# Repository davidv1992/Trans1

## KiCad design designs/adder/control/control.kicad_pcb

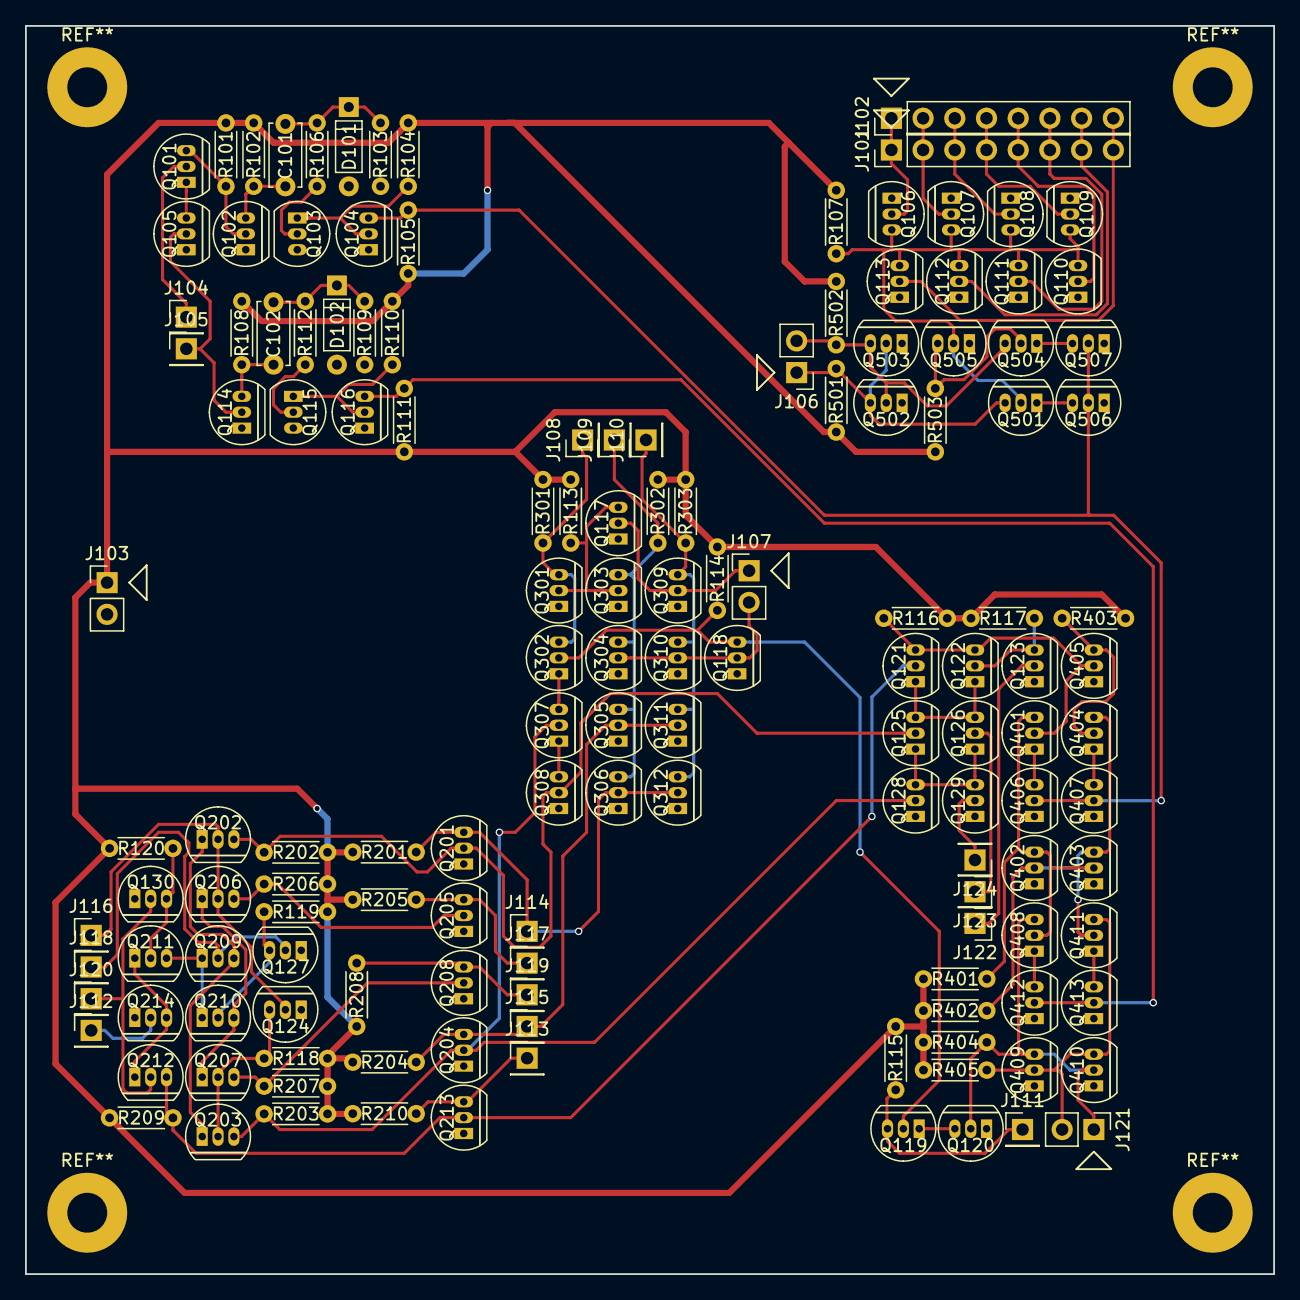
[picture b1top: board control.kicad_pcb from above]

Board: 2 copper layers, 100.0 x 100.0 mm, 145 parts (0 on the bottom side), 78 nets.

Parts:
C101, C102: 4.7nF; C_default
D101, D102: 1N4148; D_default
J101, J102: Conn_01x08; PH_1x8
J103: Conn_01x02_Power; PH_1x2
J104, J105, J108, J109, J110, J111, J112, J113, J114, J115, J116, J117, J118, J119, J120, J122, J123, J124: Conn_01x01; PH_1x1
J106, J107, J121: Conn_01x02; PH_1x2
Q101, Q102, Q104, Q105, Q106, Q107, Q108, Q109, Q110, Q111, Q112, Q113, Q114, Q116, Q117, Q118, Q119, Q120, Q121, Q122, Q123, Q124, Q125, Q126, Q127, Q128, Q129, Q130, Q201, Q202, Q203, Q204, Q205, Q206, Q207, Q208, Q209, Q210, Q211, Q212, Q213, Q214, Q301, Q302, Q303, Q304, Q305, Q306, Q307, Q308, Q309, Q310, Q311, Q312, Q401, Q402, Q403, Q404, Q405, Q406, Q407, Q408, Q409, Q410, Q411, Q412, Q413, Q501, Q502, Q503, Q504, Q505, Q506, Q507: 2N7000; TO-92-FET
Q103, Q115: BC547; TO-92-BJT
R101, R102, R104, R105, R107, R108, R110, R111, R113, R114, R115, R116, R117, R118, R119, R120, R201, R202, R203, R204, R205, R206, R207, R208, R209, R210, R301, R302, R303, R401, R402, R404, R405, R501, R502, R503: 1k; R_small
R103, R106, R109, R112: 10k; R_small
R403: R; R_small

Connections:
/BDEC/1en: J110.1, Q309.3, Q310.3, Q311.3, Q312.3, R303.2
/BDEC/Ben: J108.1, Q301.3, Q302.3, R301.2
/BDEC/LSH: J114.1, Q201.3, Q306.2, Q312.2, R201.2
/BDEC/RSH: J115.1, Q204.3, Q305.2, Q311.2, R204.2
/BDEC/b0: Q117.3, Q301.2, Q303.2, R113.2
/BDEC/b1: Q118.3, Q119.2, Q302.2, R114.2
/BDEC/~B~en: J109.1, Q303.3, Q304.3, Q305.3, Q306.3, R302.2
/BDEC/~LSH: Q125.2, Q201.2, Q202.3, Q308.2, R202.2
/BDEC/~RSH: Q128.2, Q203.3, Q204.2, Q307.2, R203.2
/BDEC/~b0: J107.1, Q117.2, Q309.2
/BDEC/~b1: J107.2, Q118.2, Q304.2, Q310.2
/Cstore/D: Q121.3, Q122.3, Q401.2, Q405.2, R116.2
/Cstore/Q: J121.1, Q120.2, Q408.3, Q409.3, Q410.2, R404.2
/Cstore/clk: Q104.3, Q406.2, Q407.2, Q506.2, Q507.2, R105.2
/Cstore/~Q: J121.2, Q409.2, Q410.3, Q411.3, R405.2
/Cstore/~clk: Q116.3, Q412.2, Q413.2, R111.2
/OutDEC/ADD: J113.1, Q213.3, R210.2
/OutDEC/AND: J117.1, Q205.3, R205.2
/OutDEC/AluEN: J112.1, Q214.2
/OutDEC/OR: J119.1, Q208.3, R208.2
/OutDEC/S0: Q124.3, Q203.2, Q207.2, R118.2
/OutDEC/S1: Q127.3, Q210.2, R119.2
/OutDEC/S2: Q130.3, Q211.2, R120.2
/OutDEC/~ADD: Q121.2, Q212.3, Q213.2, R209.2
/OutDEC/~AND: Q205.2, Q206.3, R206.2
/OutDEC/~OR: Q207.3, Q208.2, R207.2
/OutDEC/~S0: J116.1, Q124.2, Q202.2, Q206.2
/OutDEC/~S1: J118.1, Q127.2, Q209.2
/OutDEC/~S2: J120.1, Q130.2, Q212.2
/Zstore/D: Q106.3, Q107.3, Q108.3, Q109.3, Q110.3, Q111.3, Q112.3, Q113.3, Q501.2, Q505.2, R107.2
/Zstore/Q: J106.2, Q502.2, Q503.3, Q504.3, R502.2
/Zstore/~Q: J106.1, Q501.3, Q502.3, Q503.2, R501.2
GND: D101.2, D102.2, J103.2, Q102.1, Q103.3, Q104.1, Q105.1, Q106.1, Q107.1, Q108.1, Q109.1, Q110.1, Q111.1, Q112.1, Q113.1, Q114.1, Q115.3, Q116.1, Q117.1, Q118.1, Q120.1, Q123.1, Q124.1, Q127.1, Q128.1, Q129.1, Q130.1, Q201.1, Q204.1, Q205.1, Q208.1, Q213.1, Q214.1, Q301.1, Q303.1, Q304.1, Q305.1, Q306.1, Q308.1, Q309.1, Q310.1, Q311.1, Q312.1, Q402.1, Q403.1, Q405.1, Q406.1, Q407.1, Q409.1, Q410.1, Q412.1, Q413.1, Q502.1, Q503.1, Q505.1, Q506.1, Q507.1, R103.1, R109.1
unnamed: C101.1, D101.1, R103.2, R106.2
unnamed: C101.2, Q102.3, R102.2
unnamed: C102.1, D102.1, R109.2, R112.2
unnamed: C102.2, Q114.3, R108.2
unnamed: J101.1, J102.1, Q106.2
unnamed: J101.2, J102.2, Q107.2
unnamed: J101.3, J102.3, Q108.2
unnamed: J101.4, J102.4, Q109.2
unnamed: J101.5, J102.5, Q110.2
unnamed: J101.6, J102.6, Q111.2
unnamed: J101.7, J102.7, Q112.2
unnamed: J101.8, J102.8, Q113.2
unnamed: J104.1, Q101.2
unnamed: J105.1, Q105.2, Q114.2
unnamed: J111.1, Q119.3, R115.2
unnamed: J122.1, Q123.2
unnamed: J123.1, Q126.2
unnamed: J124.1, Q129.2
unnamed: Q101.1, Q105.3
unnamed: Q101.3, Q102.2, R101.2
unnamed: Q103.1, Q104.2, R104.2
unnamed: Q103.2, R106.1
unnamed: Q115.1, Q116.2, R110.2
unnamed: Q115.2, R112.1
unnamed: Q119.1, Q120.3
unnamed: Q121.1, Q122.1, Q125.3, Q126.3
unnamed: Q122.2, Q123.3, R117.2
unnamed: Q125.1, Q126.1, Q128.3, Q129.3
unnamed: Q202.1, Q203.1, Q209.3
unnamed: Q206.1, Q207.1, Q210.3
unnamed: Q209.1, Q210.1, Q211.3
unnamed: Q211.1, Q212.1, Q214.3
unnamed: Q302.1, Q307.3
unnamed: Q307.1, Q308.3
unnamed: Q401.1, Q406.3
unnamed: Q401.3, Q402.3, Q403.2, Q408.2, R401.2
unnamed: Q402.2, Q403.3, Q404.3, Q411.2, R402.2
unnamed: Q404.1, Q407.3
unnamed: Q404.2, Q405.3, R403.2
unnamed: Q408.1, Q412.3
unnamed: Q411.1, Q413.3
unnamed: Q501.1, Q506.3
unnamed: Q504.1, Q507.3
unnamed: Q504.2, Q505.3, R503.2
VCC: J103.1, R101.1, R102.1, R104.1, R105.1, R107.1, R108.1, R110.1, R111.1, R113.1, R114.1, R115.1, R116.1, R117.1, R118.1, R119.1, R120.1, R201.1, R202.1, R203.1, R204.1, R205.1, R206.1, R207.1, R208.1, R209.1, R210.1, R301.1, R302.1, R303.1, R401.1, R402.1, R403.1, R404.1, R405.1, R501.1, R502.1, R503.1

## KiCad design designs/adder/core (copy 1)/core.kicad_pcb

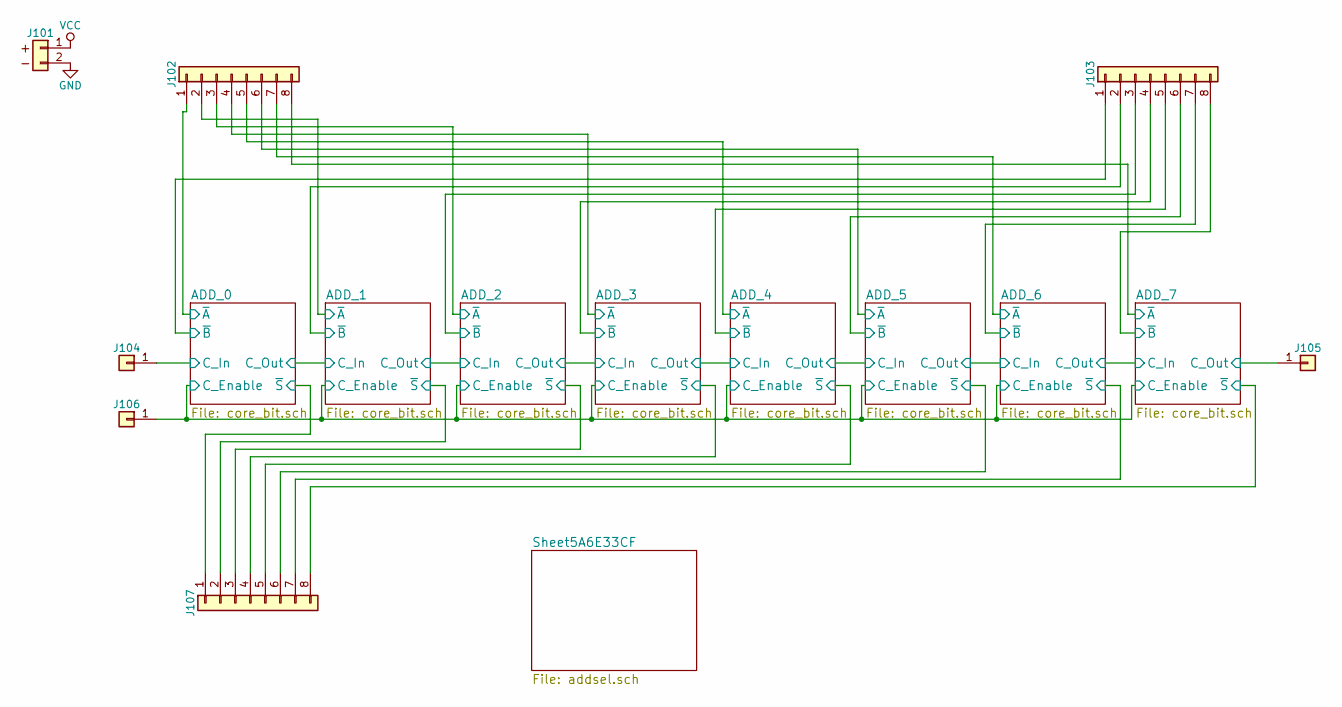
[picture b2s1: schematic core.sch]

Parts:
J101: Conn_01x02_Power; PH_1x2
J102, J103, J107: Conn_01x08; PH_1x8
J104, J105, J106: Conn_01x01; PH_1x1

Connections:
/ADD_0/C_Enable: J106.1; also elsewhere on the board
/ADD_0/C_In: J104.1; also elsewhere on the board
/ADD_0/~A~: J102.1; also elsewhere on the board
/ADD_0/~B~: J103.1; also elsewhere on the board
/ADD_0/~S~: J107.1; also elsewhere on the board
/ADD_1/~A~: J102.2; also elsewhere on the board
/ADD_1/~B~: J103.2; also elsewhere on the board
/ADD_1/~S~: J107.2; also elsewhere on the board
/ADD_2/~A~: J102.3; also elsewhere on the board
/ADD_2/~B~: J103.3; also elsewhere on the board
/ADD_2/~S~: J107.3; also elsewhere on the board
/ADD_3/~A~: J102.4; also elsewhere on the board
/ADD_3/~B~: J103.4; also elsewhere on the board
/ADD_3/~S~: J107.4; also elsewhere on the board
/ADD_4/~A~: J102.5; also elsewhere on the board
/ADD_4/~B~: J103.5; also elsewhere on the board
/ADD_4/~S~: J107.5; also elsewhere on the board
/ADD_5/~A~: J102.6; also elsewhere on the board
/ADD_5/~B~: J103.6; also elsewhere on the board
/ADD_5/~S~: J107.6; also elsewhere on the board
/ADD_6/~A~: J102.7; also elsewhere on the board
/ADD_6/~B~: J103.7; also elsewhere on the board
/ADD_6/~S~: J107.7; also elsewhere on the board
/ADD_7/C_Out: J105.1; also elsewhere on the board
/ADD_7/~A~: J102.8; also elsewhere on the board
/ADD_7/~B~: J103.8; also elsewhere on the board
/ADD_7/~S~: J107.8; also elsewhere on the board
GND: J101.2; also elsewhere on the board
VCC: J101.1; also elsewhere on the board

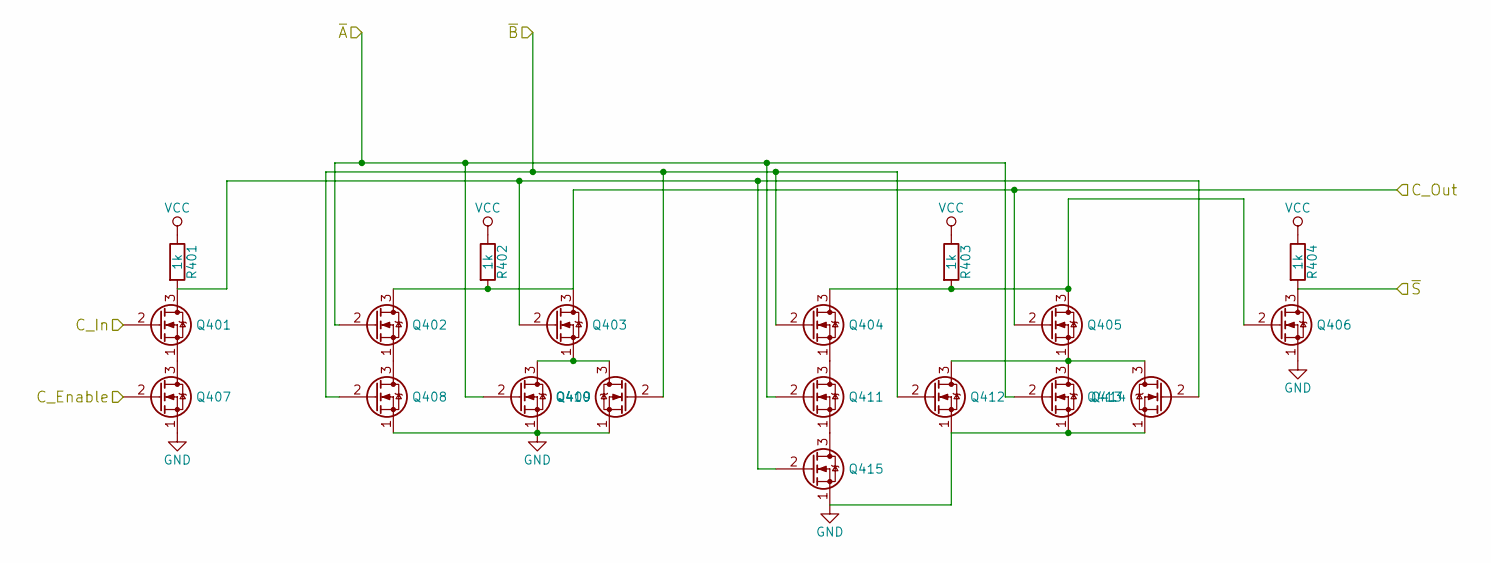
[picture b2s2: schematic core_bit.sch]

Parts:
Q201, Q202, Q203, Q204, Q205, Q206, Q207, Q208, Q209, Q210, Q211, Q212, Q213, Q214, Q215: 2N7000; TO-92-FET
R201, R202, R203, R204: 1k; R_small

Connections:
/ADD_0/C_Enable: Q207.2 (G); also elsewhere on the board
/ADD_0/C_In: Q201.2 (G); also elsewhere on the board
/ADD_0/~A~: Q202.2 (G), Q209.2 (G), Q211.2 (G), Q213.2 (G); also elsewhere on the board
/ADD_0/~B~: Q204.2 (G), Q208.2 (G), Q210.2 (G), Q212.2 (G); also elsewhere on the board
/ADD_0/~S~: Q206.3 (D), R204.2; also elsewhere on the board
/ADD_1/C_In: Q202.3 (D), Q203.3 (D), Q205.2 (G), R202.2; also elsewhere on the board
GND: Q206.1 (S), Q207.1 (S), Q208.1 (S), Q209.1 (S), Q210.1 (S), Q212.1 (S), Q213.1 (S), Q214.1 (S), Q215.1 (S); also elsewhere on the board
unnamed: Q201.1 (S), Q207.3 (D)
unnamed: Q201.3 (D), Q203.2 (G), Q214.2 (G), Q215.2 (G), R201.2
unnamed: Q202.1 (S), Q208.3 (D)
unnamed: Q203.1 (S), Q209.3 (D), Q210.3 (D)
unnamed: Q204.1 (S), Q211.3 (D)
unnamed: Q204.3 (D), Q205.3 (D), Q206.2 (G), R203.2
unnamed: Q205.1 (S), Q212.3 (D), Q213.3 (D), Q214.3 (D)
unnamed: Q211.1 (S), Q215.3 (D)
VCC: R201.1, R202.1, R203.1, R204.1; also elsewhere on the board

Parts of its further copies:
Q301, Q302, Q303, Q304, Q305, Q306, Q307, Q308, Q309, Q310, Q311, Q312, Q313, Q314, Q315, Q401, Q402, Q403, Q404, Q405, Q406, Q407, Q408, Q409, Q410, Q411, Q412, Q413, Q414, Q415, Q501, Q502, Q503, Q504, Q505, Q506, Q507, Q508, Q509, Q510, Q511, Q512, Q513, Q514, Q515, Q601, Q602, Q603, Q604, Q605, Q606, Q607, Q608, Q609, Q610, Q611, Q612, Q613, Q614, Q615, Q701, Q702, Q703, Q704, Q705, Q706, Q707, Q708, Q709, Q710, Q711, Q712, Q713, Q714, Q715, Q801, Q802, Q803, Q804, Q805, Q806, Q807, Q808, Q809, Q810, Q811, Q812, Q813, Q814, Q815, Q901, Q902, Q903, Q904, Q905, Q906, Q907, Q908, Q909, Q910, Q911, Q912, Q913, Q914, Q915: 2N7000; TO-92-FET
R301, R302, R303, R304, R401, R402, R403, R404, R501, R502, R503, R504, R601, R602, R603, R604, R701, R702, R703, R704, R801, R802, R803, R804, R901, R902, R903, R904: 1k; R_small

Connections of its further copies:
/ADD_0/C_Enable: Q307.2 (G), Q407.2 (G), Q507.2 (G), Q607.2 (G), Q707.2 (G), Q807.2 (G), Q907.2 (G); also elsewhere on the board
/ADD_1/C_In: Q301.2 (G); also elsewhere on the board
/ADD_1/~A~: Q302.2 (G), Q309.2 (G), Q311.2 (G), Q313.2 (G); also elsewhere on the board
/ADD_1/~B~: Q304.2 (G), Q308.2 (G), Q310.2 (G), Q312.2 (G); also elsewhere on the board
/ADD_1/~S~: Q306.3 (D), R304.2; also elsewhere on the board
/ADD_2/C_In: Q302.3 (D), Q303.3 (D), Q305.2 (G), Q401.2 (G), R302.2
/ADD_2/~A~: Q402.2 (G), Q409.2 (G), Q411.2 (G), Q413.2 (G); also elsewhere on the board
/ADD_2/~B~: Q404.2 (G), Q408.2 (G), Q410.2 (G), Q412.2 (G); also elsewhere on the board
/ADD_2/~S~: Q406.3 (D), R404.2; also elsewhere on the board
/ADD_3/C_In: Q402.3 (D), Q403.3 (D), Q405.2 (G), Q501.2 (G), R402.2
/ADD_3/~A~: Q502.2 (G), Q509.2 (G), Q511.2 (G), Q513.2 (G); also elsewhere on the board
/ADD_3/~B~: Q504.2 (G), Q508.2 (G), Q510.2 (G), Q512.2 (G); also elsewhere on the board
/ADD_3/~S~: Q506.3 (D), R504.2; also elsewhere on the board
/ADD_4/C_In: Q502.3 (D), Q503.3 (D), Q505.2 (G), Q601.2 (G), R502.2
/ADD_4/~A~: Q602.2 (G), Q609.2 (G), Q611.2 (G), Q613.2 (G); also elsewhere on the board
/ADD_4/~B~: Q604.2 (G), Q608.2 (G), Q610.2 (G), Q612.2 (G); also elsewhere on the board
/ADD_4/~S~: Q606.3 (D), R604.2; also elsewhere on the board
/ADD_5/C_In: Q602.3 (D), Q603.3 (D), Q605.2 (G), Q701.2 (G), R602.2
/ADD_5/~A~: Q702.2 (G), Q709.2 (G), Q711.2 (G), Q713.2 (G); also elsewhere on the board
/ADD_5/~B~: Q704.2 (G), Q708.2 (G), Q710.2 (G), Q712.2 (G); also elsewhere on the board
/ADD_5/~S~: Q706.3 (D), R704.2; also elsewhere on the board
/ADD_6/C_In: Q702.3 (D), Q703.3 (D), Q705.2 (G), Q801.2 (G), R702.2
/ADD_6/~A~: Q802.2 (G), Q809.2 (G), Q811.2 (G), Q813.2 (G); also elsewhere on the board
/ADD_6/~B~: Q804.2 (G), Q808.2 (G), Q810.2 (G), Q812.2 (G); also elsewhere on the board
/ADD_6/~S~: Q806.3 (D), R804.2; also elsewhere on the board
/ADD_7/C_In: Q802.3 (D), Q803.3 (D), Q805.2 (G), Q901.2 (G), R802.2
/ADD_7/C_Out: Q902.3 (D), Q903.3 (D), Q905.2 (G), R902.2; also elsewhere on the board
/ADD_7/~A~: Q902.2 (G), Q909.2 (G), Q911.2 (G), Q913.2 (G); also elsewhere on the board
/ADD_7/~B~: Q904.2 (G), Q908.2 (G), Q910.2 (G), Q912.2 (G); also elsewhere on the board
/ADD_7/~S~: Q906.3 (D), R904.2; also elsewhere on the board
GND: Q306.1 (S), Q307.1 (S), Q308.1 (S), Q309.1 (S), Q310.1 (S), Q312.1 (S), Q313.1 (S), Q314.1 (S), Q315.1 (S), Q406.1 (S), Q407.1 (S), Q408.1 (S), Q409.1 (S), Q410.1 (S), Q412.1 (S), Q413.1 (S), Q414.1 (S), Q415.1 (S), Q506.1 (S), Q507.1 (S), Q508.1 (S), Q509.1 (S), Q510.1 (S), Q512.1 (S), Q513.1 (S), Q514.1 (S), Q515.1 (S), Q606.1 (S), Q607.1 (S), Q608.1 (S), Q609.1 (S), Q610.1 (S), Q612.1 (S), Q613.1 (S), Q614.1 (S), Q615.1 (S), Q706.1 (S), Q707.1 (S), Q708.1 (S), Q709.1 (S), Q710.1 (S), Q712.1 (S), Q713.1 (S), Q714.1 (S), Q715.1 (S), Q806.1 (S), Q807.1 (S), Q808.1 (S), Q809.1 (S), Q810.1 (S), Q812.1 (S), Q813.1 (S), Q814.1 (S), Q815.1 (S), Q906.1 (S), Q907.1 (S), Q908.1 (S), Q909.1 (S), Q910.1 (S), Q912.1 (S), Q913.1 (S), Q914.1 (S), Q915.1 (S); also elsewhere on the board
unnamed: Q301.1 (S), Q307.3 (D)
unnamed: Q301.3 (D), Q303.2 (G), Q314.2 (G), Q315.2 (G), R301.2
unnamed: Q302.1 (S), Q308.3 (D)
unnamed: Q303.1 (S), Q309.3 (D), Q310.3 (D)
unnamed: Q304.1 (S), Q311.3 (D)
unnamed: Q304.3 (D), Q305.3 (D), Q306.2 (G), R303.2
unnamed: Q305.1 (S), Q312.3 (D), Q313.3 (D), Q314.3 (D)
unnamed: Q311.1 (S), Q315.3 (D)
unnamed: Q401.1 (S), Q407.3 (D)
unnamed: Q401.3 (D), Q403.2 (G), Q414.2 (G), Q415.2 (G), R401.2
unnamed: Q402.1 (S), Q408.3 (D)
unnamed: Q403.1 (S), Q409.3 (D), Q410.3 (D)
unnamed: Q404.1 (S), Q411.3 (D)
unnamed: Q404.3 (D), Q405.3 (D), Q406.2 (G), R403.2
unnamed: Q405.1 (S), Q412.3 (D), Q413.3 (D), Q414.3 (D)
unnamed: Q411.1 (S), Q415.3 (D)
unnamed: Q501.1 (S), Q507.3 (D)
unnamed: Q501.3 (D), Q503.2 (G), Q514.2 (G), Q515.2 (G), R501.2
unnamed: Q502.1 (S), Q508.3 (D)
unnamed: Q503.1 (S), Q509.3 (D), Q510.3 (D)
unnamed: Q504.1 (S), Q511.3 (D)
unnamed: Q504.3 (D), Q505.3 (D), Q506.2 (G), R503.2
unnamed: Q505.1 (S), Q512.3 (D), Q513.3 (D), Q514.3 (D)
unnamed: Q511.1 (S), Q515.3 (D)
unnamed: Q601.1 (S), Q607.3 (D)
unnamed: Q601.3 (D), Q603.2 (G), Q614.2 (G), Q615.2 (G), R601.2
unnamed: Q602.1 (S), Q608.3 (D)
unnamed: Q603.1 (S), Q609.3 (D), Q610.3 (D)
unnamed: Q604.1 (S), Q611.3 (D)
unnamed: Q604.3 (D), Q605.3 (D), Q606.2 (G), R603.2
unnamed: Q605.1 (S), Q612.3 (D), Q613.3 (D), Q614.3 (D)
unnamed: Q611.1 (S), Q615.3 (D)
unnamed: Q701.1 (S), Q707.3 (D)
unnamed: Q701.3 (D), Q703.2 (G), Q714.2 (G), Q715.2 (G), R701.2
unnamed: Q702.1 (S), Q708.3 (D)
unnamed: Q703.1 (S), Q709.3 (D), Q710.3 (D)
unnamed: Q704.1 (S), Q711.3 (D)
unnamed: Q704.3 (D), Q705.3 (D), Q706.2 (G), R703.2
unnamed: Q705.1 (S), Q712.3 (D), Q713.3 (D), Q714.3 (D)
unnamed: Q711.1 (S), Q715.3 (D)
unnamed: Q801.1 (S), Q807.3 (D)
unnamed: Q801.3 (D), Q803.2 (G), Q814.2 (G), Q815.2 (G), R801.2
unnamed: Q802.1 (S), Q808.3 (D)
unnamed: Q803.1 (S), Q809.3 (D), Q810.3 (D)
unnamed: Q804.1 (S), Q811.3 (D)
unnamed: Q804.3 (D), Q805.3 (D), Q806.2 (G), R803.2
unnamed: Q805.1 (S), Q812.3 (D), Q813.3 (D), Q814.3 (D)
unnamed: Q811.1 (S), Q815.3 (D)
unnamed: Q901.1 (S), Q907.3 (D)
unnamed: Q901.3 (D), Q903.2 (G), Q914.2 (G), Q915.2 (G), R901.2
unnamed: Q902.1 (S), Q908.3 (D)
unnamed: Q903.1 (S), Q909.3 (D), Q910.3 (D)
unnamed: Q904.1 (S), Q911.3 (D)
unnamed: Q904.3 (D), Q905.3 (D), Q906.2 (G), R903.2
unnamed: Q905.1 (S), Q912.3 (D), Q913.3 (D), Q914.3 (D)
unnamed: Q911.1 (S), Q915.3 (D)
VCC: R301.1, R302.1, R303.1, R304.1, R401.1, R402.1, R403.1, R404.1, R501.1, R502.1, R503.1, R504.1, R601.1, R602.1, R603.1, R604.1, R701.1, R702.1, R703.1, R704.1, R801.1, R802.1, R803.1, R804.1, R901.1, R902.1, R903.1, R904.1; also elsewhere on the board

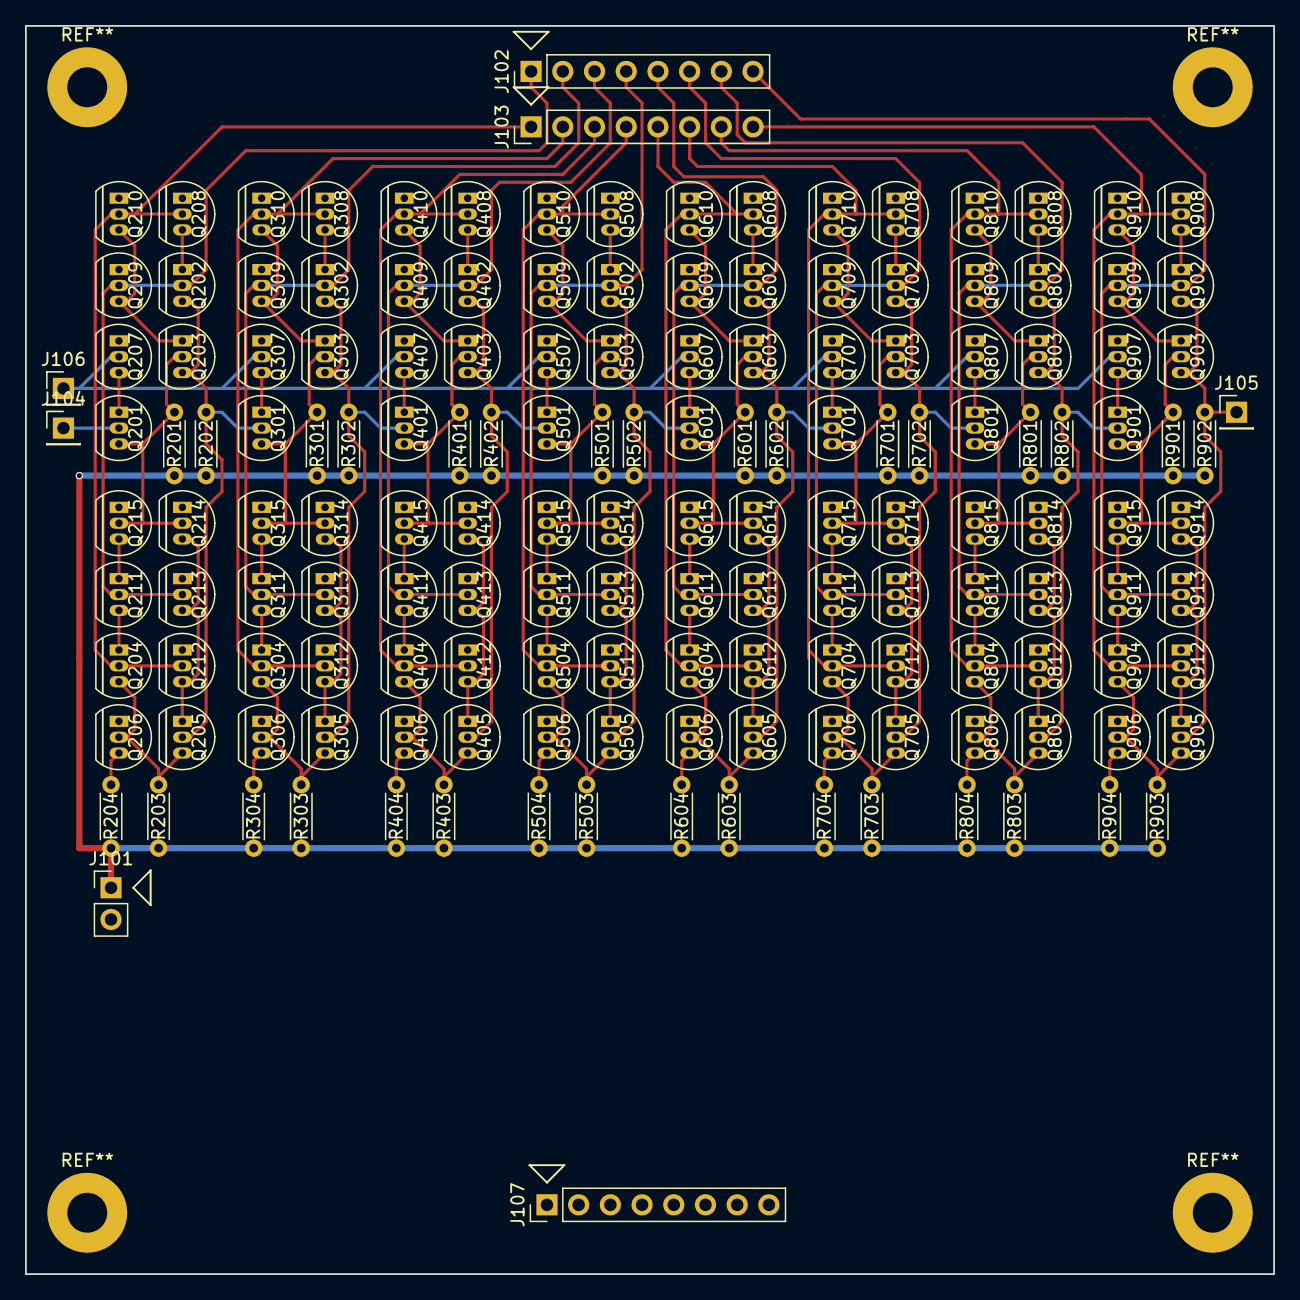
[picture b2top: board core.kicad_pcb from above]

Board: 2 copper layers, 100.0 x 100.0 mm, 159 parts (0 on the bottom side), 100 nets.

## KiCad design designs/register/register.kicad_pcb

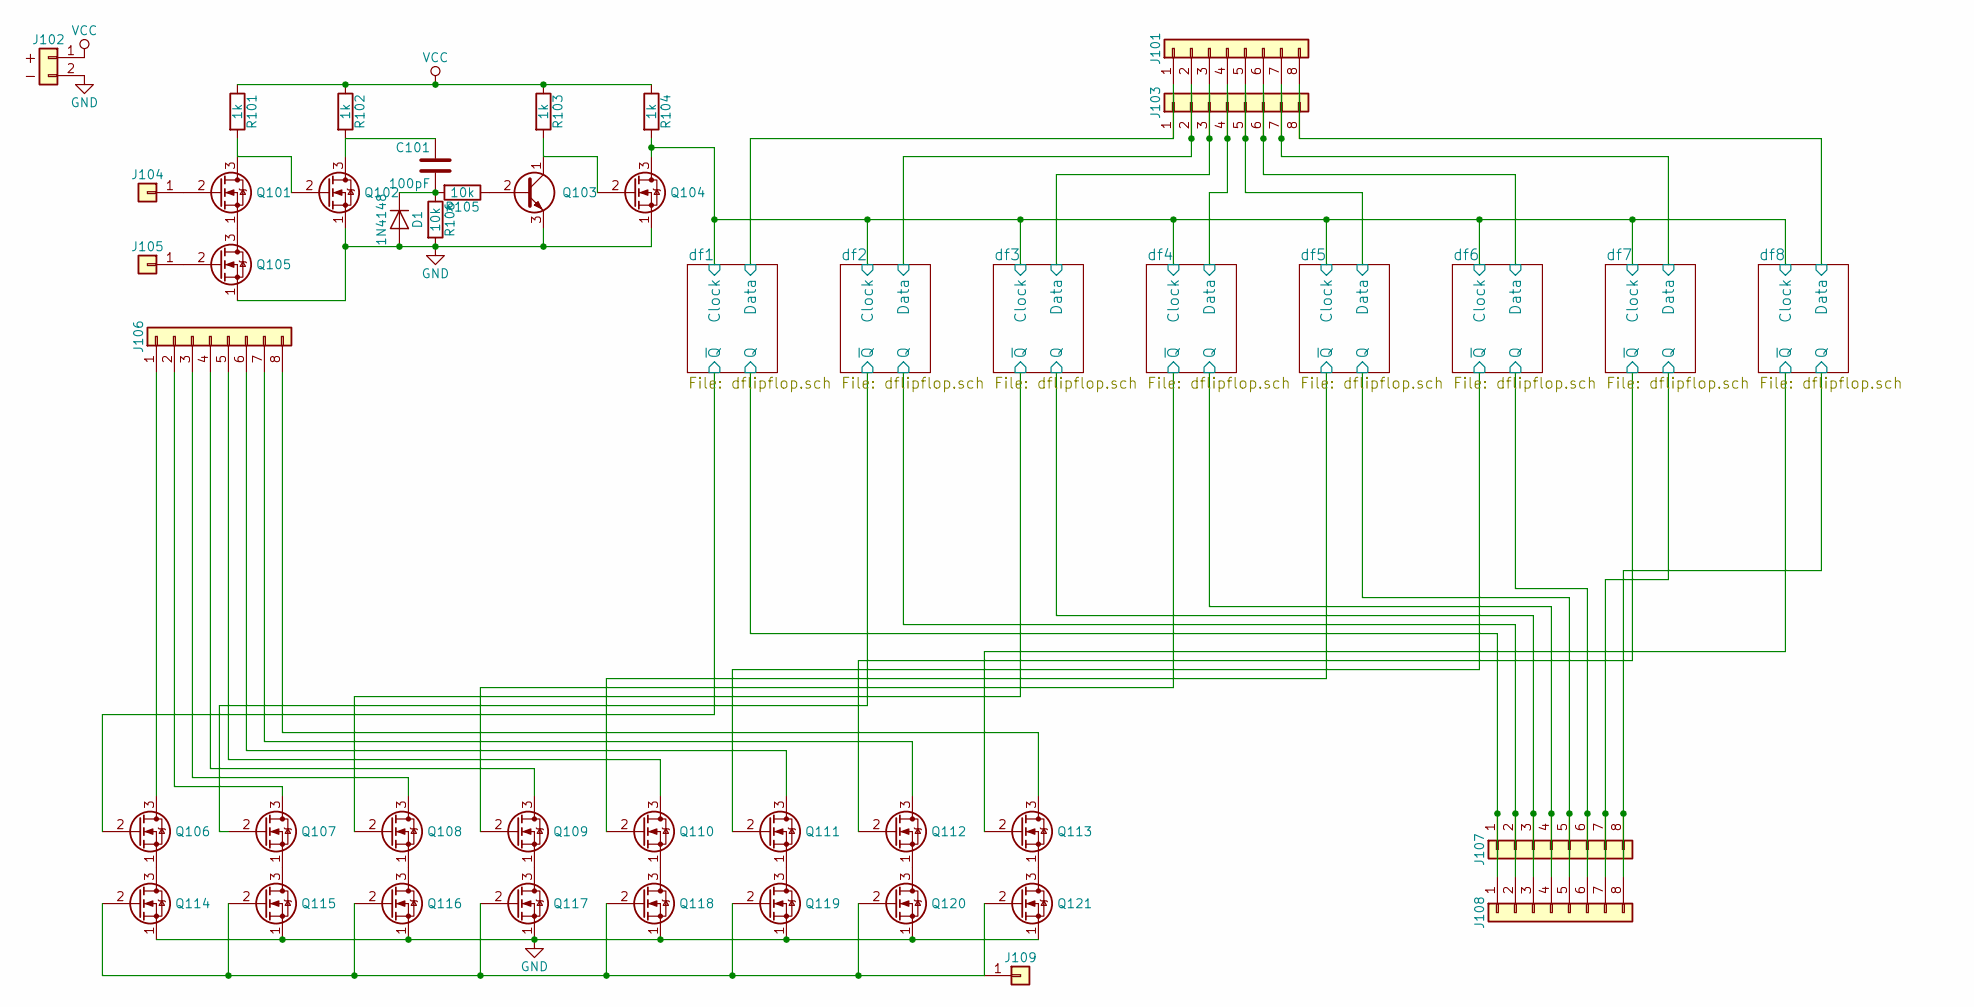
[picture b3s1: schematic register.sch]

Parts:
C101: 100pF; C_default
D1: 1N4148; D_default
J101, J103, J106, J107, J108: Conn_01x08; PH_1x8
J102: Conn_01x02_Power; PH_1x2
J104, J105, J109: Conn_01x01; PH_1x1
Q101, Q102, Q104, Q105, Q106, Q107, Q108, Q109, Q110, Q111, Q112, Q113, Q114, Q115, Q116, Q117, Q118, Q119, Q120, Q121: 2N7000; TO-92-FET
Q103: BC547; TO-92-BJT
R101, R102, R103, R104: 1k; R_small
R105, R106: 10k; R_small

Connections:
/df1/Clock: Q104.3 (D), R104.2; also elsewhere on the board
/df1/Data: J101.1, J103.1; also elsewhere on the board
/df1/Q: J107.1, J108.1; also elsewhere on the board
/df1/~Q~: Q106.2 (G); also elsewhere on the board
/df2/Data: J101.2, J103.2; also elsewhere on the board
/df2/Q: J107.2, J108.2; also elsewhere on the board
/df2/~Q~: Q107.2 (G); also elsewhere on the board
/df3/Data: J101.3, J103.3; also elsewhere on the board
/df3/Q: J107.3, J108.3; also elsewhere on the board
/df3/~Q~: Q108.2 (G); also elsewhere on the board
/df4/Data: J101.4, J103.4; also elsewhere on the board
/df4/Q: J107.4, J108.4; also elsewhere on the board
/df4/~Q~: Q109.2 (G); also elsewhere on the board
/df5/Data: J101.5, J103.5; also elsewhere on the board
/df5/Q: J107.5, J108.5; also elsewhere on the board
/df5/~Q~: Q110.2 (G); also elsewhere on the board
/df6/Data: J101.6, J103.6; also elsewhere on the board
/df6/Q: J107.6, J108.6; also elsewhere on the board
/df6/~Q~: Q111.2 (G); also elsewhere on the board
/df7/Data: J101.7, J103.7; also elsewhere on the board
/df7/Q: J107.7, J108.7; also elsewhere on the board
/df7/~Q~: Q112.2 (G); also elsewhere on the board
/df8/Data: J101.8, J103.8; also elsewhere on the board
/df8/Q: J107.8, J108.8; also elsewhere on the board
/df8/~Q~: Q113.2 (G); also elsewhere on the board
GND: D1.2 (A), J102.2, Q102.1 (S), Q103.3 (E), Q104.1 (S), Q105.1 (S), Q114.1 (S), Q115.1 (S), Q116.1 (S), Q117.1 (S), Q118.1 (S), Q119.1 (S), Q120.1 (S), Q121.1 (S), R106.2; also elsewhere on the board
unnamed: C101.1, Q102.3 (D), R102.2
unnamed: C101.2, D1.1 (K), R105.2, R106.1
unnamed: J104.1, Q101.2 (G)
unnamed: J105.1, Q105.2 (G)
unnamed: J106.1, Q106.3 (D)
unnamed: J106.2, Q107.3 (D)
unnamed: J106.3, Q108.3 (D)
unnamed: J106.4, Q109.3 (D)
unnamed: J106.5, Q110.3 (D)
unnamed: J106.6, Q111.3 (D)
unnamed: J106.7, Q112.3 (D)
unnamed: J106.8, Q113.3 (D)
unnamed: J109.1, Q114.2 (G), Q115.2 (G), Q116.2 (G), Q117.2 (G), Q118.2 (G), Q119.2 (G), Q120.2 (G), Q121.2 (G)
unnamed: Q101.1 (S), Q105.3 (D)
unnamed: Q101.3 (D), Q102.2 (G), R101.2
unnamed: Q103.1 (C), Q104.2 (G), R103.2
unnamed: Q103.2 (B), R105.1
unnamed: Q106.1 (S), Q114.3 (D)
unnamed: Q107.1 (S), Q115.3 (D)
unnamed: Q108.1 (S), Q116.3 (D)
unnamed: Q109.1 (S), Q117.3 (D)
unnamed: Q110.1 (S), Q118.3 (D)
unnamed: Q111.1 (S), Q119.3 (D)
unnamed: Q112.1 (S), Q120.3 (D)
unnamed: Q113.1 (S), Q121.3 (D)
VCC: J102.1, R101.1, R102.1, R103.1, R104.1; also elsewhere on the board

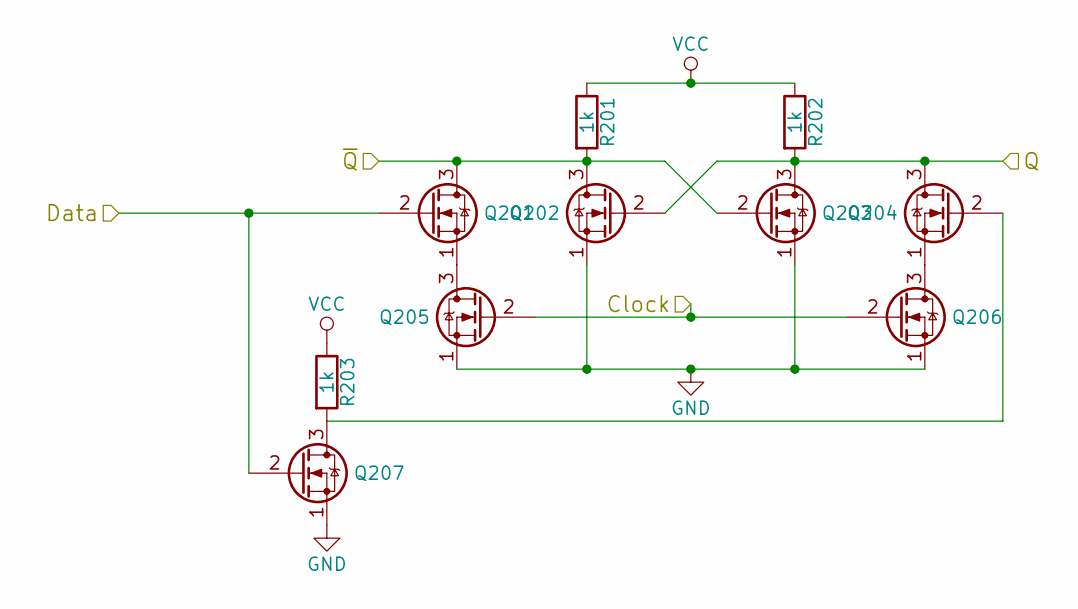
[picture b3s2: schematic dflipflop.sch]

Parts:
Q201, Q202, Q203, Q204, Q205, Q206, Q207: 2N7000; TO-92-FET
R201, R202, R203: 1k; R_small

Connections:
/df1/Clock: Q205.2 (G), Q206.2 (G); also elsewhere on the board
/df1/Data: Q201.2 (G), Q207.2 (G); also elsewhere on the board
/df1/Q: Q202.2 (G), Q203.3 (D), Q204.3 (D), R202.2; also elsewhere on the board
/df1/~Q~: Q201.3 (D), Q202.3 (D), Q203.2 (G), R201.2; also elsewhere on the board
GND: Q202.1 (S), Q203.1 (S), Q205.1 (S), Q206.1 (S), Q207.1 (S); also elsewhere on the board
unnamed: Q201.1 (S), Q205.3 (D)
unnamed: Q204.1 (S), Q206.3 (D)
unnamed: Q204.2 (G), Q207.3 (D), R203.2
VCC: R201.1, R202.1, R203.1; also elsewhere on the board

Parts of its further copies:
Q301, Q302, Q303, Q304, Q305, Q306, Q307, Q401, Q402, Q403, Q404, Q405, Q406, Q407, Q501, Q502, Q503, Q504, Q505, Q506, Q507, Q601, Q602, Q603, Q604, Q605, Q606, Q607, Q701, Q702, Q703, Q704, Q705, Q706, Q707, Q801, Q802, Q803, Q804, Q805, Q806, Q807, Q901, Q902, Q903, Q904, Q905, Q906, Q907: 2N7000; TO-92-FET
R301, R302, R303, R401, R402, R403, R501, R502, R503, R601, R602, R603, R701, R702, R703, R801, R802, R803, R901, R902, R903: 1k; R_small

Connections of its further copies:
/df1/Clock: Q305.2 (G), Q306.2 (G), Q405.2 (G), Q406.2 (G), Q505.2 (G), Q506.2 (G), Q605.2 (G), Q606.2 (G), Q705.2 (G), Q706.2 (G), Q805.2 (G), Q806.2 (G), Q905.2 (G), Q906.2 (G); also elsewhere on the board
/df2/Data: Q301.2 (G), Q307.2 (G); also elsewhere on the board
/df2/Q: Q302.2 (G), Q303.3 (D), Q304.3 (D), R302.2; also elsewhere on the board
/df2/~Q~: Q301.3 (D), Q302.3 (D), Q303.2 (G), R301.2; also elsewhere on the board
/df3/Data: Q401.2 (G), Q407.2 (G); also elsewhere on the board
/df3/Q: Q402.2 (G), Q403.3 (D), Q404.3 (D), R402.2; also elsewhere on the board
/df3/~Q~: Q401.3 (D), Q402.3 (D), Q403.2 (G), R401.2; also elsewhere on the board
/df4/Data: Q501.2 (G), Q507.2 (G); also elsewhere on the board
/df4/Q: Q502.2 (G), Q503.3 (D), Q504.3 (D), R502.2; also elsewhere on the board
/df4/~Q~: Q501.3 (D), Q502.3 (D), Q503.2 (G), R501.2; also elsewhere on the board
/df5/Data: Q601.2 (G), Q607.2 (G); also elsewhere on the board
/df5/Q: Q602.2 (G), Q603.3 (D), Q604.3 (D), R602.2; also elsewhere on the board
/df5/~Q~: Q601.3 (D), Q602.3 (D), Q603.2 (G), R601.2; also elsewhere on the board
/df6/Data: Q701.2 (G), Q707.2 (G); also elsewhere on the board
/df6/Q: Q702.2 (G), Q703.3 (D), Q704.3 (D), R702.2; also elsewhere on the board
/df6/~Q~: Q701.3 (D), Q702.3 (D), Q703.2 (G), R701.2; also elsewhere on the board
/df7/Data: Q801.2 (G), Q807.2 (G); also elsewhere on the board
/df7/Q: Q802.2 (G), Q803.3 (D), Q804.3 (D), R802.2; also elsewhere on the board
/df7/~Q~: Q801.3 (D), Q802.3 (D), Q803.2 (G), R801.2; also elsewhere on the board
/df8/Data: Q901.2 (G), Q907.2 (G); also elsewhere on the board
/df8/Q: Q902.2 (G), Q903.3 (D), Q904.3 (D), R902.2; also elsewhere on the board
/df8/~Q~: Q901.3 (D), Q902.3 (D), Q903.2 (G), R901.2; also elsewhere on the board
GND: Q302.1 (S), Q303.1 (S), Q305.1 (S), Q306.1 (S), Q307.1 (S), Q402.1 (S), Q403.1 (S), Q405.1 (S), Q406.1 (S), Q407.1 (S), Q502.1 (S), Q503.1 (S), Q505.1 (S), Q506.1 (S), Q507.1 (S), Q602.1 (S), Q603.1 (S), Q605.1 (S), Q606.1 (S), Q607.1 (S), Q702.1 (S), Q703.1 (S), Q705.1 (S), Q706.1 (S), Q707.1 (S), Q802.1 (S), Q803.1 (S), Q805.1 (S), Q806.1 (S), Q807.1 (S), Q902.1 (S), Q903.1 (S), Q905.1 (S), Q906.1 (S), Q907.1 (S); also elsewhere on the board
unnamed: Q301.1 (S), Q305.3 (D)
unnamed: Q304.1 (S), Q306.3 (D)
unnamed: Q304.2 (G), Q307.3 (D), R303.2
unnamed: Q401.1 (S), Q405.3 (D)
unnamed: Q404.1 (S), Q406.3 (D)
unnamed: Q404.2 (G), Q407.3 (D), R403.2
unnamed: Q501.1 (S), Q505.3 (D)
unnamed: Q504.1 (S), Q506.3 (D)
unnamed: Q504.2 (G), Q507.3 (D), R503.2
unnamed: Q601.1 (S), Q605.3 (D)
unnamed: Q604.1 (S), Q606.3 (D)
unnamed: Q604.2 (G), Q607.3 (D), R603.2
unnamed: Q701.1 (S), Q705.3 (D)
unnamed: Q704.1 (S), Q706.3 (D)
unnamed: Q704.2 (G), Q707.3 (D), R703.2
unnamed: Q801.1 (S), Q805.3 (D)
unnamed: Q804.1 (S), Q806.3 (D)
unnamed: Q804.2 (G), Q807.3 (D), R803.2
unnamed: Q901.1 (S), Q905.3 (D)
unnamed: Q904.1 (S), Q906.3 (D)
unnamed: Q904.2 (G), Q907.3 (D), R903.2
VCC: R301.1, R302.1, R303.1, R401.1, R402.1, R403.1, R501.1, R502.1, R503.1, R601.1, R602.1, R603.1, R701.1, R702.1, R703.1, R801.1, R802.1, R803.1, R901.1, R902.1, R903.1; also elsewhere on the board

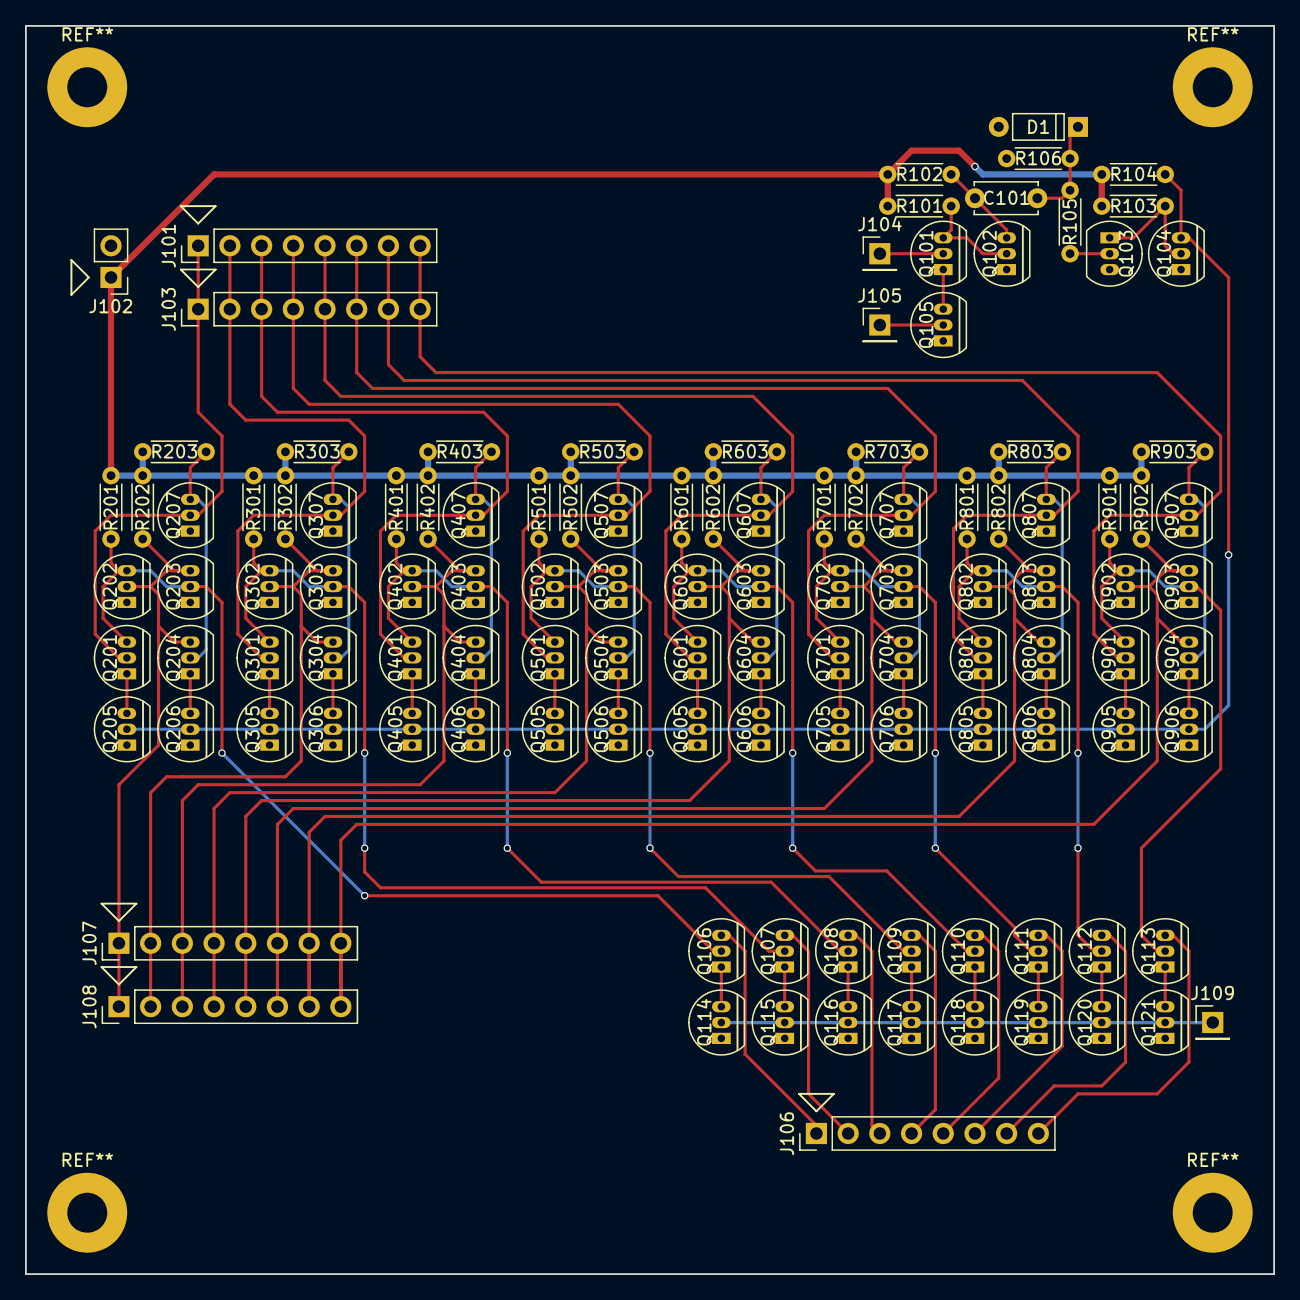
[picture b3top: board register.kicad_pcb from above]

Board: 2 copper layers, 100.0 x 100.0 mm, 118 parts (0 on the bottom side), 76 nets.
